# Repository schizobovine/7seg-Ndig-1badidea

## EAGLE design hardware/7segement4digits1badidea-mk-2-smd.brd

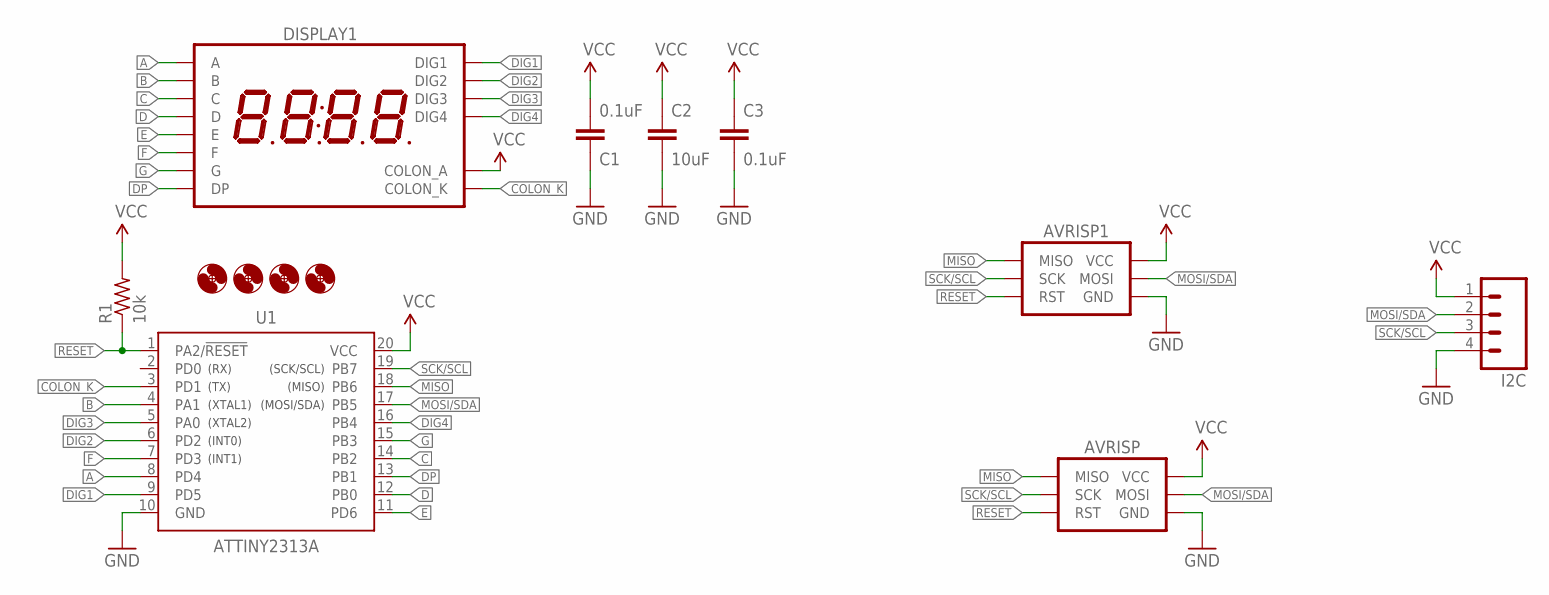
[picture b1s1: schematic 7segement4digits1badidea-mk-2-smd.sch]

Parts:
AVRISP: AVR_SPI_PRG_6PTH; 2X3
AVRISP1: AVR_SPI_PRG_6SMD-RA-FLOPPED-I2C; 1X06-SMD
C1, C3: 0.1uF; C0805
C2: 10uF; C0805
DISPLAY1: 7SED_4DIGIT_14MM14.2MM-CC; 7SEG_4DIG
H1, H2, H3, H4: HOLE#2; HOLE-#2
I2C: M04PTH; 1X04-PTH-VERT
R1: 10k; R0805
U1: ATTINY2313A; SOP20W

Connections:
A: DISPLAY1.P$13 (A), U1.8 (PD4)
B: DISPLAY1.P$9 (B), U1.4 (PA1)
C: DISPLAY1.P$4 (C), U1.14 (PB2)
COLON_K: DISPLAY1.P$7 (COLON_K), U1.3 (PD1)
D: DISPLAY1.P$2 (D), U1.12 (PB0)
DIG1: DISPLAY1.P$14 (DIG1), U1.9 (PD5)
DIG2: DISPLAY1.P$11 (DIG2), U1.6 (PD2)
DIG3: DISPLAY1.P$10 (DIG3), U1.5 (PA0)
DIG4: DISPLAY1.P$6 (DIG4), U1.16 (PB4)
DP: DISPLAY1.P$3 (DP), U1.13 (PB1)
E: DISPLAY1.P$1 (E), U1.11 (PD6)
F: DISPLAY1.P$12 (F), U1.7 (PD3)
G: DISPLAY1.P$5 (G), U1.15 (PB3)
GND: AVRISP.6 (GND), AVRISP1.4 (GND), C1.1, C2.2, C3.2, I2C.4, U1.10 (GND)
MISO: AVRISP.1 (MISO), AVRISP1.5 (MISO), U1.18 (PB6)
MOSI/SDA: AVRISP.4 (MOSI), AVRISP1.3 (MOSI), I2C.2, U1.17 (PB5)
RESET: AVRISP.5 (RST), AVRISP1.6 (RST), R1.1, U1.1 (PA2/!RESET)
SCK/SCL: AVRISP.3 (SCK), AVRISP1.2 (SCK), I2C.3, U1.19 (PB7)
VCC: AVRISP.2 (VCC), AVRISP1.1 (VCC), C1.2, C2.1, C3.1, DISPLAY1.P$8 (COLON_A), I2C.1, R1.2, U1.20 (VCC)

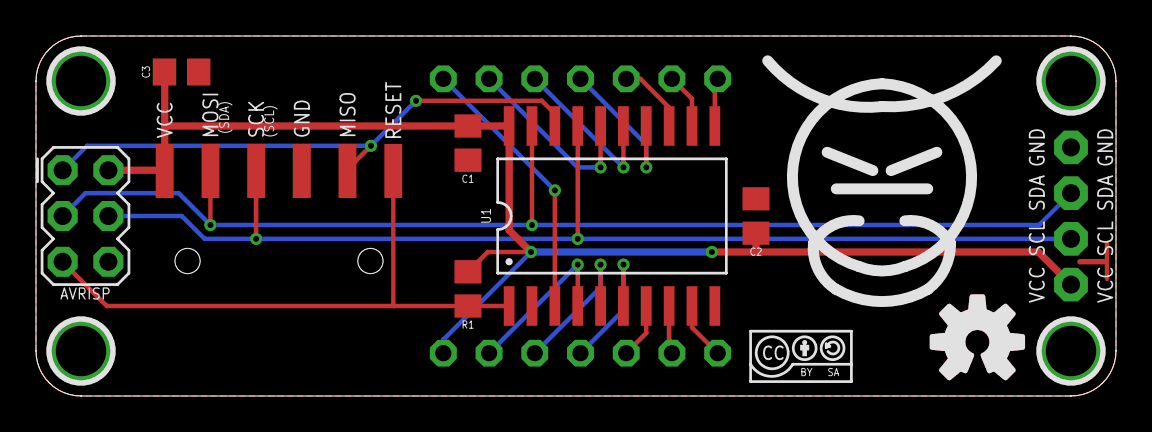
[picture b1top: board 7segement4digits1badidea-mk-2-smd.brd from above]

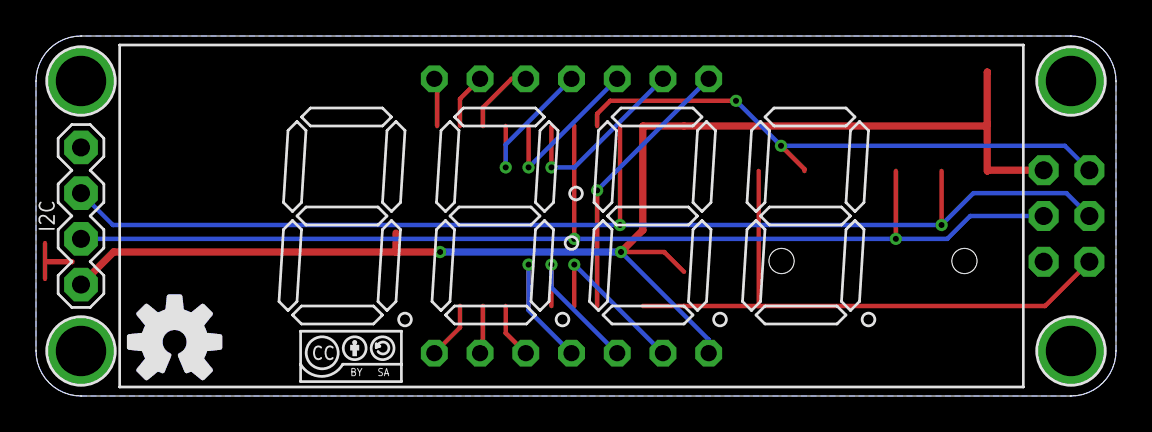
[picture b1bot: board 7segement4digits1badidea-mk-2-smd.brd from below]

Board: 2 copper layers, 60.0 x 20.0 mm, 18 parts (4 on the bottom side), 19 nets.

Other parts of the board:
U$1: COW
U$2, U$5: CC-BY-SA-4.0-NO-URL
U$3, U$4: OSHWLOGO_TOP_0.2_A

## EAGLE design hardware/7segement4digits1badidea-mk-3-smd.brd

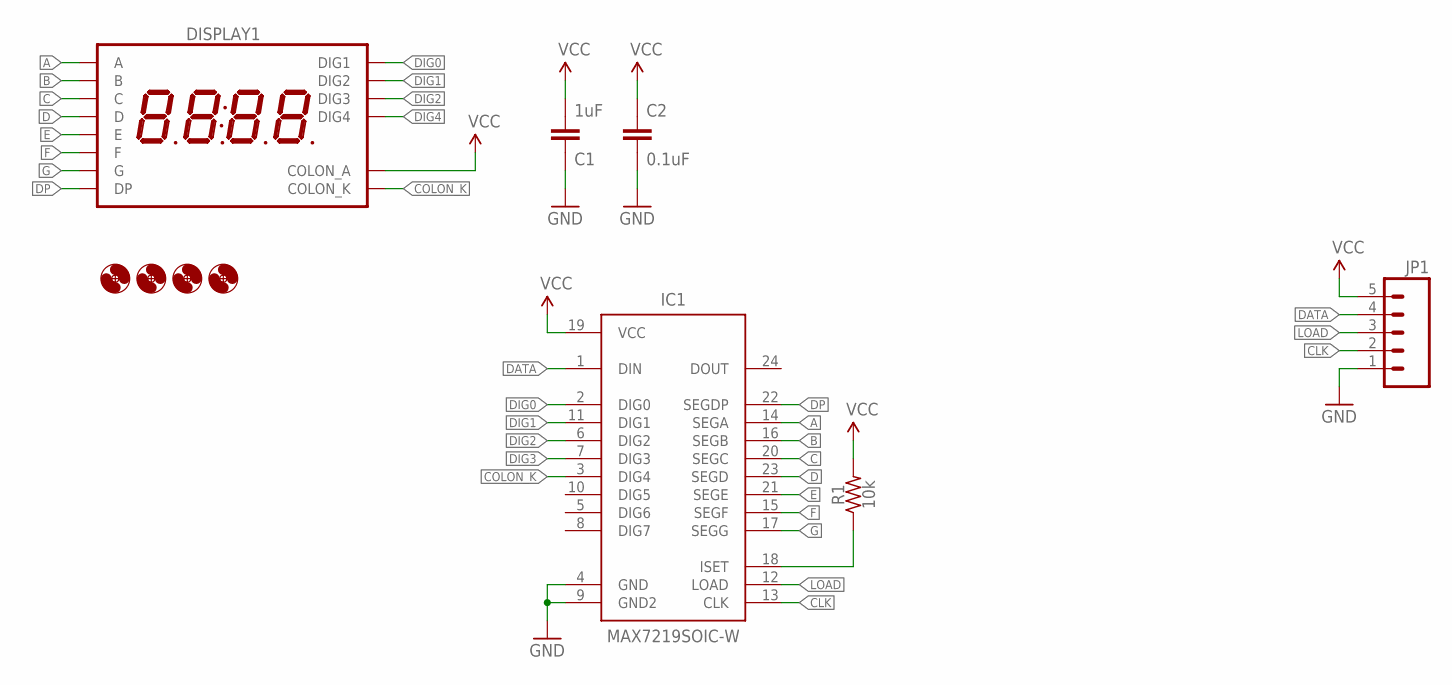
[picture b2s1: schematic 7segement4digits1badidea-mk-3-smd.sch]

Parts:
C1: 1uF; C0805
C2: 0.1uF; C0603
DISPLAY1: 7SEG_4DIGIT_COLONLOLSMDWAT; 7SEG_4DIG_0.56IN_14MM_ADAFRUIT_LOL_SMD_WAT
H1, H2, H3, H4: HOLE#2; HOLE-#2
IC1: MAX7219SOIC-W; SO24W
JP1: M05JST-PH-VERT-PTH; JST-5-PH-VERT-PTH
R1: 10k; R0603

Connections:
A: DISPLAY1.P$13 (A), IC1.14 (SEGA)
B: DISPLAY1.P$9 (B), IC1.16 (SEGB)
C: DISPLAY1.P$4 (C), IC1.20 (SEGC)
CLK: IC1.13 (CLK), JP1.2
COLON_K: DISPLAY1.P$7 (COLON_K), IC1.3 (DIG4)
D: DISPLAY1.P$2 (D), IC1.23 (SEGD)
DATA: IC1.1 (DIN), JP1.4
DIG0: DISPLAY1.P$14 (DIG1), IC1.2 (DIG0)
DIG1: DISPLAY1.P$11 (DIG2), IC1.11 (DIG1)
DIG2: DISPLAY1.P$10 (DIG3), IC1.6 (DIG2)
DIG3: IC1.7 (DIG3)
DIG4: DISPLAY1.P$6 (DIG4)
DP: DISPLAY1.P$3 (DP), IC1.22 (SEGDP)
E: DISPLAY1.P$1 (E), IC1.21 (SEGE)
F: DISPLAY1.P$12 (F), IC1.15 (SEGF)
G: DISPLAY1.P$5 (G), IC1.17 (SEGG)
GND: C1.1, C2.2, IC1.4 (GND), IC1.9 (GND2), JP1.1
LOAD: IC1.12 (LOAD), JP1.3
unnamed: IC1.18 (ISET), R1.1
VCC: C1.2, C2.1, DISPLAY1.P$8 (COLON_A), IC1.19 (VCC), JP1.5, R1.2

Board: 2 copper layers, 14 parts (2 on the bottom side), 18 nets, no tracks yet.

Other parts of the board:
U$1: COW
U$2, U$5: CC-BY-SA-4.0-NO-URL
U$3: OSHWLOGO_TOP_0.2_A

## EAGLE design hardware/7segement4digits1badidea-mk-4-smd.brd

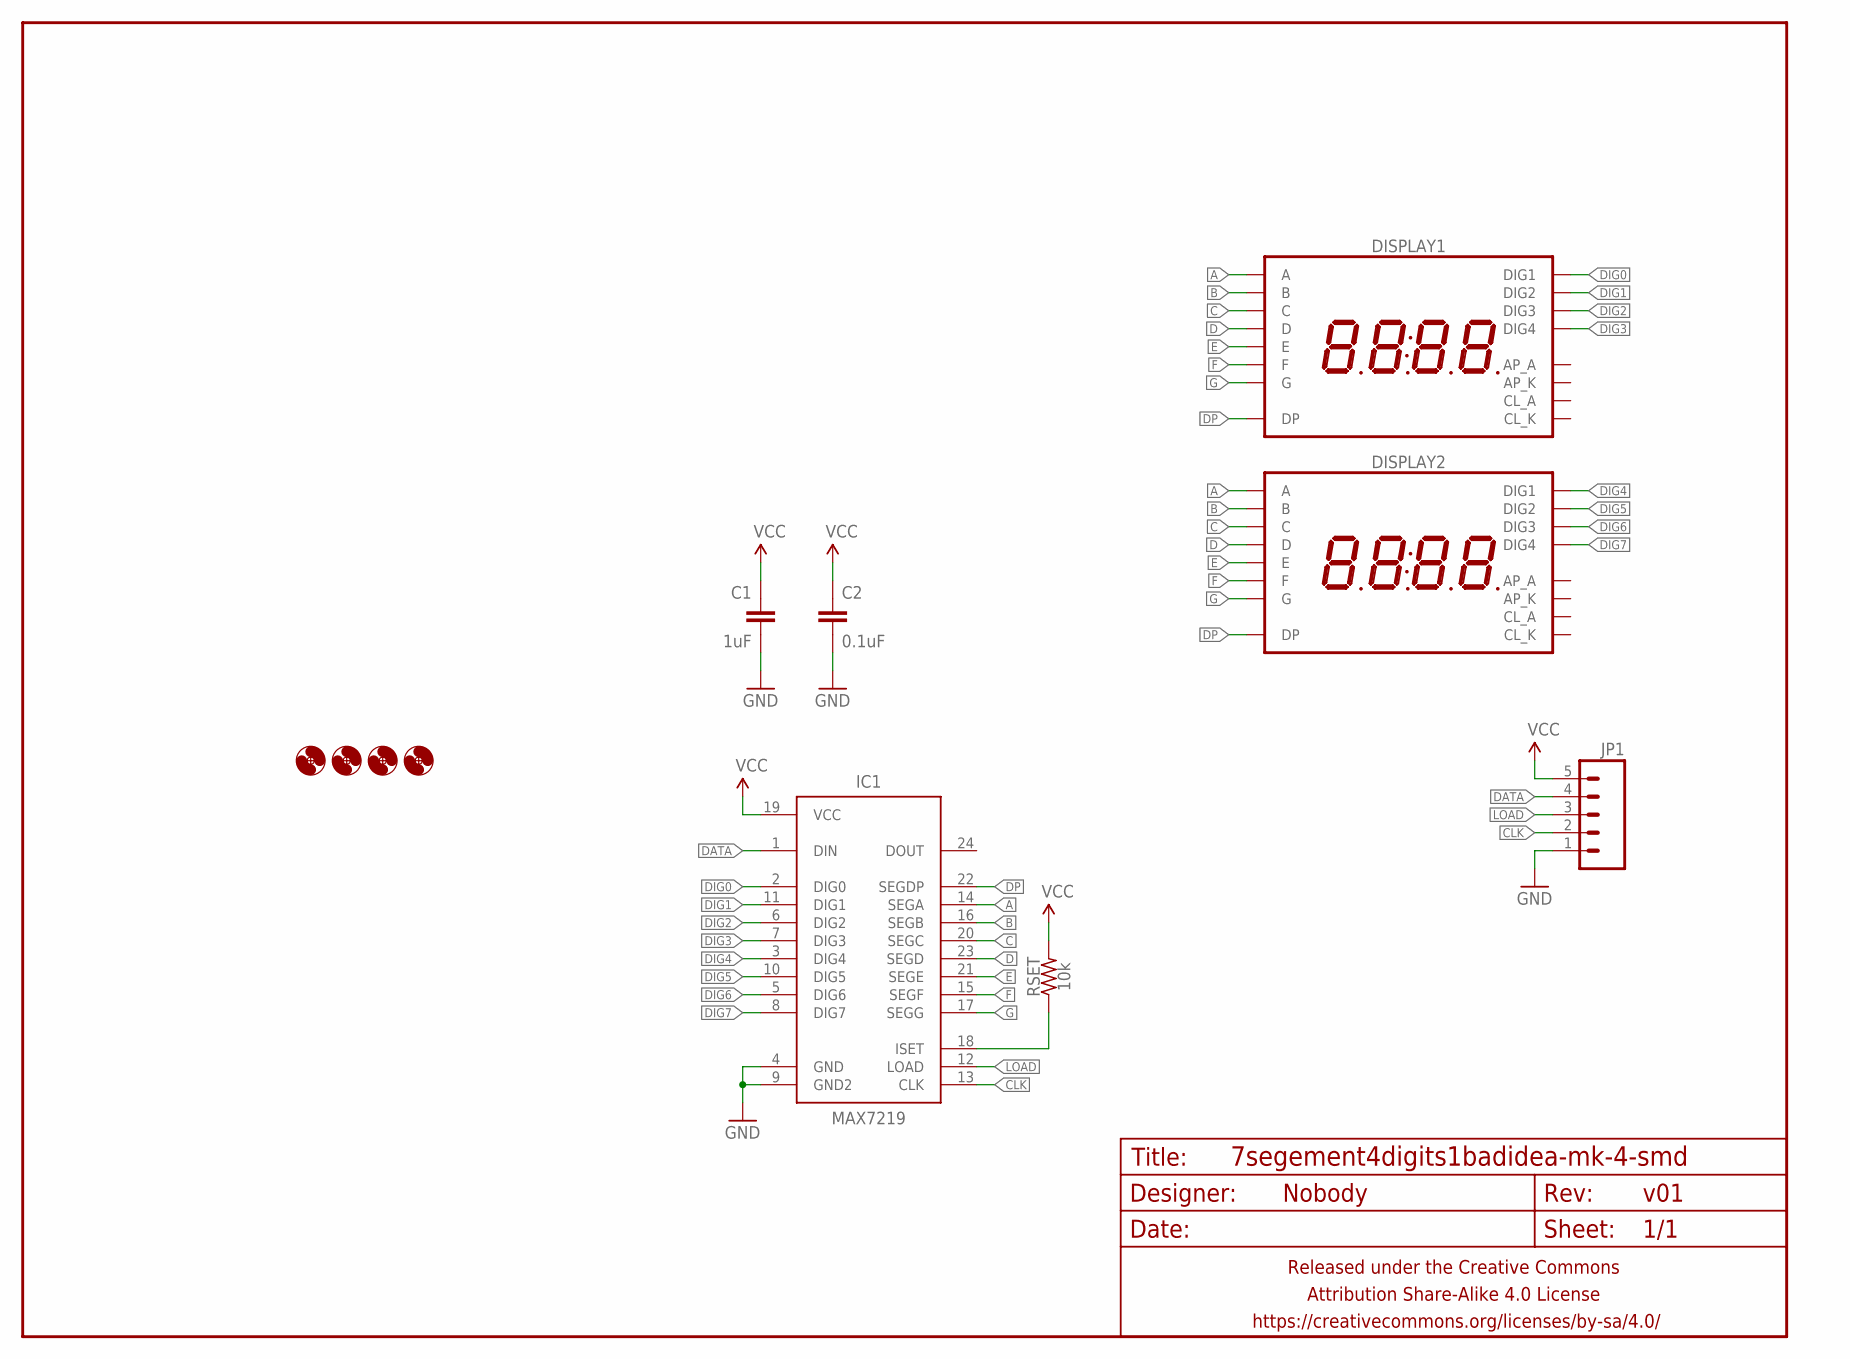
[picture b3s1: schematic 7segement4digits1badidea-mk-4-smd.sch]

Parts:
C1: 1uF; C025-024X044
C2: 0.1uF; C025-024X044
DISPLAY1, DISPLAY2: 7SEG_4DIGIT_COLON_APOS; 7SEG_4DIG_10MM
FRAME1: FRAME-LETTERNO_PACKAGE; DUMMY
H1, H2, H3, H4: HOLE#2; HOLE-#2
IC1: MAX7219; SO24W
JP1: M05PTH; 1X05
RSET: 10k; RESISTOR-AXIAL-PTH-6.35MM

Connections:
A: DISPLAY1.14 (A), DISPLAY2.14 (A), IC1.14 (SEGA)
B: DISPLAY1.16 (B), DISPLAY2.16 (B), IC1.16 (SEGB)
C: DISPLAY1.13 (C), DISPLAY2.13 (C), IC1.20 (SEGC)
CLK: IC1.13 (CLK), JP1.2
D: DISPLAY1.3 (D), DISPLAY2.3 (D), IC1.23 (SEGD)
DATA: IC1.1 (DIN), JP1.4
DIG0: DISPLAY1.1 (DIG1), IC1.2 (DIG0)
DIG1: DISPLAY1.2 (DIG2), IC1.11 (DIG1)
DIG2: DISPLAY1.6 (DIG3), IC1.6 (DIG2)
DIG3: DISPLAY1.8 (DIG4), IC1.7 (DIG3)
DIG4: DISPLAY2.1 (DIG1), IC1.3 (DIG4)
DIG5: DISPLAY2.2 (DIG2), IC1.10 (DIG5)
DIG6: DISPLAY2.6 (DIG3), IC1.5 (DIG6)
DIG7: DISPLAY2.8 (DIG4), IC1.8 (DIG7)
DP: DISPLAY1.7 (DP), DISPLAY2.7 (DP), IC1.22 (SEGDP)
E: DISPLAY1.5 (E), DISPLAY2.5 (E), IC1.21 (SEGE)
F: DISPLAY1.11 (F), DISPLAY2.11 (F), IC1.15 (SEGF)
G: DISPLAY1.15 (G), DISPLAY2.15 (G), IC1.17 (SEGG)
GND: C1.2, C2.2, IC1.4 (GND), IC1.9 (GND2), JP1.1
LOAD: IC1.12 (LOAD), JP1.3
unnamed: IC1.18 (ISET), RSET.P$1 (1)
VCC: C1.1, C2.1, IC1.19 (VCC), JP1.5, RSET.P$2 (2)

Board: 2 copper layers, 12 parts (2 on the bottom side), 22 nets, no tracks yet.

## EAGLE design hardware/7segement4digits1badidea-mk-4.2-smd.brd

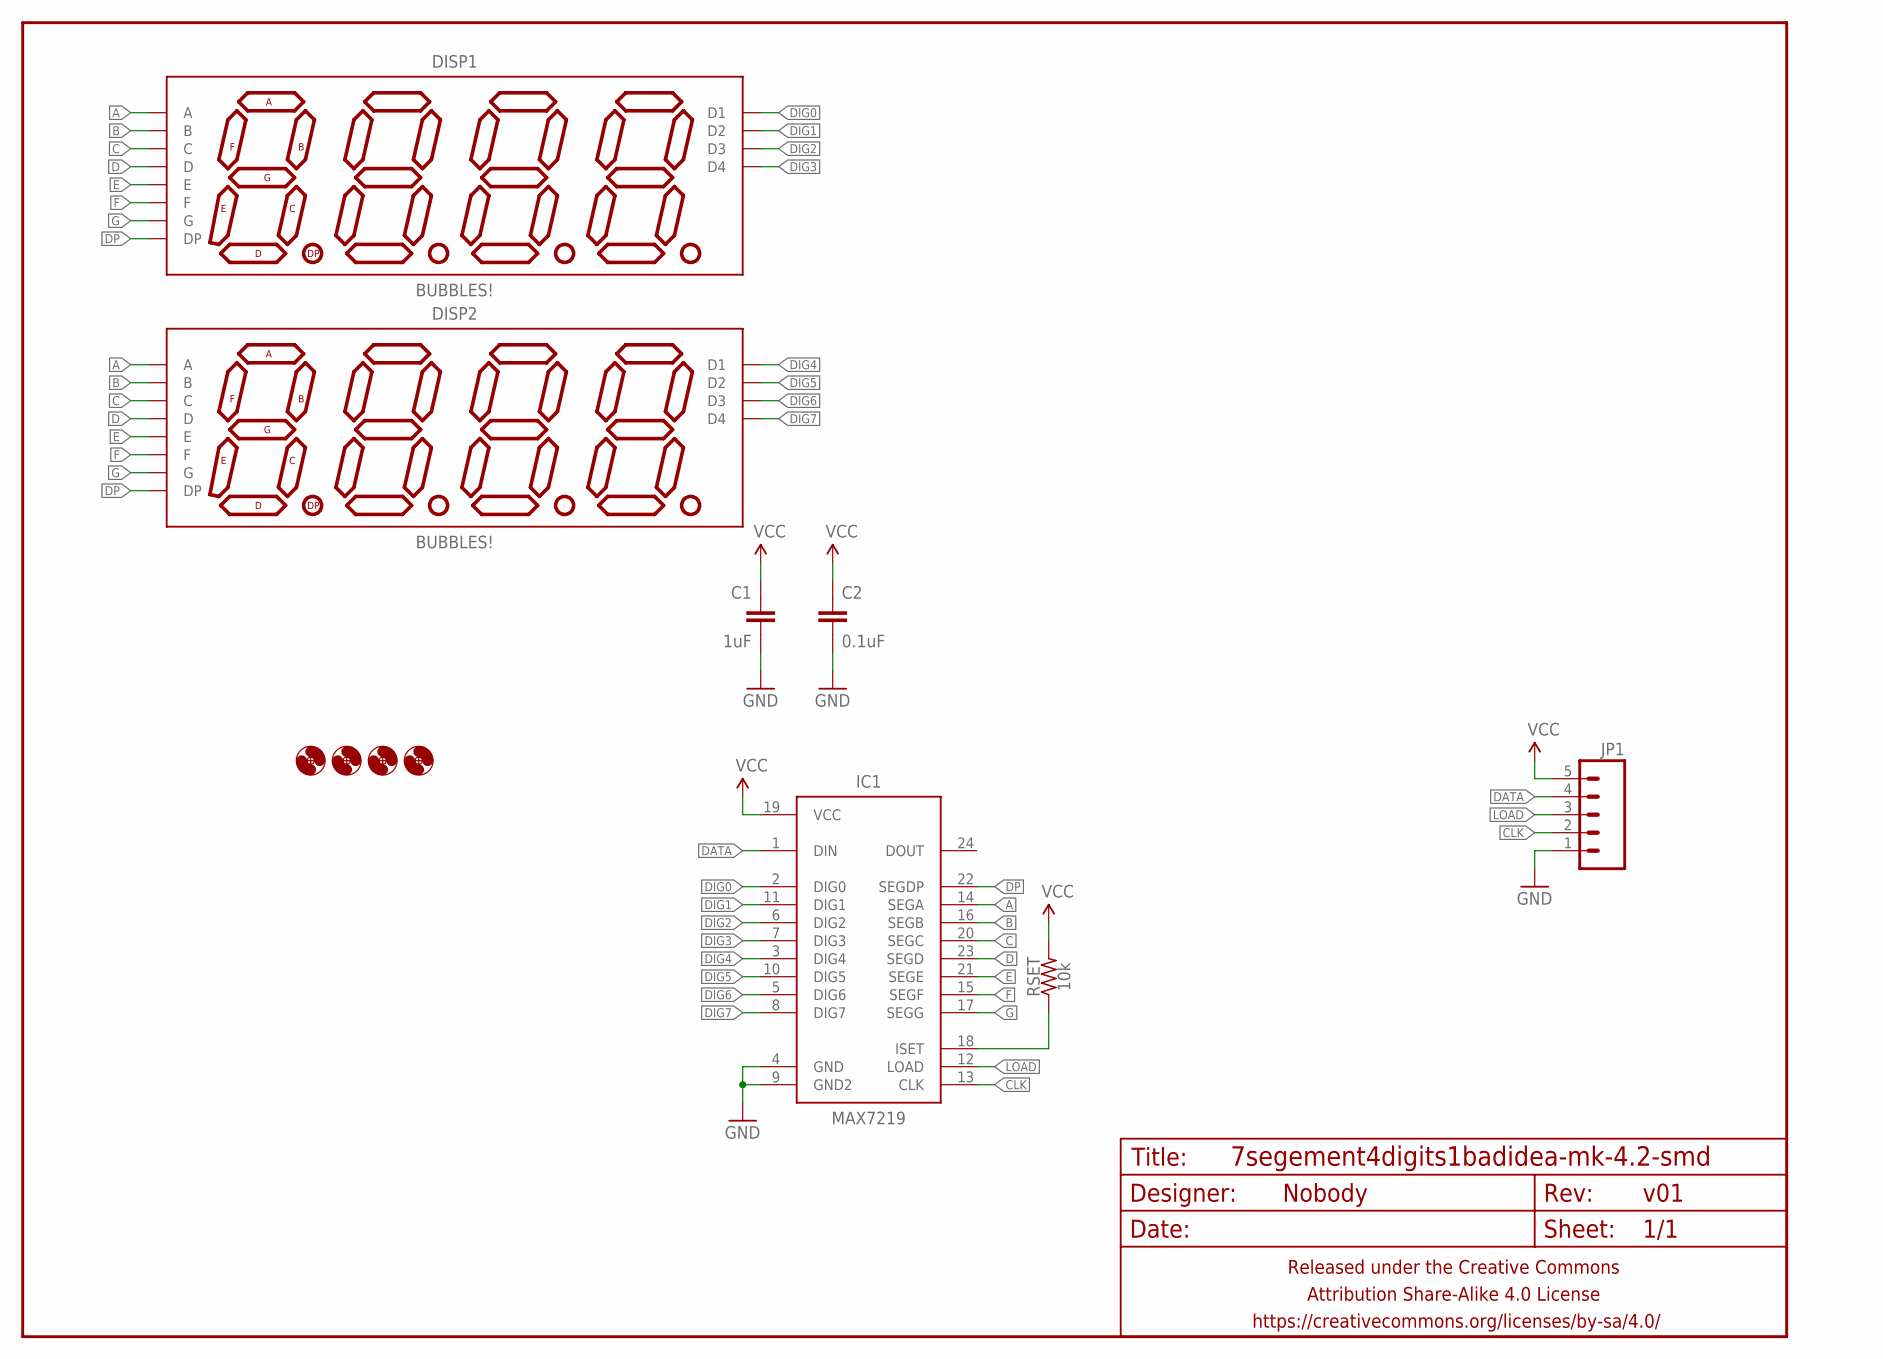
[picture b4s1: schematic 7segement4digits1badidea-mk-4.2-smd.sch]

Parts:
C1: 1uF; C025-024X044
C2: 0.1uF; C025-024X044
DISP1, DISP2: BUBBLES!; DIL12
FRAME1: FRAME-LETTERNO_PACKAGE; DUMMY
H1, H2, H3, H4: HOLE#2; HOLE-#2
IC1: MAX7219; SO24W
JP1: M05PTH; 1X05
RSET: 10k; RESISTOR-AXIAL-PTH-6.35MM

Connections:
A: DISP1.12 (A), DISP2.12 (A), IC1.14 (SEGA)
B: DISP1.11 (B), DISP2.11 (B), IC1.16 (SEGB)
C: DISP1.3 (C), DISP2.3 (C), IC1.20 (SEGC)
CLK: IC1.13 (CLK), JP1.2
D: DISP1.8 (D), DISP2.8 (D), IC1.23 (SEGD)
DATA: IC1.1 (DIN), JP1.4
DIG0: DISP1.1 (D1), IC1.2 (DIG0)
DIG1: DISP1.10 (D2), IC1.11 (DIG1)
DIG2: DISP1.4 (D3), IC1.6 (DIG2)
DIG3: DISP1.6 (D4), IC1.7 (DIG3)
DIG4: DISP2.1 (D1), IC1.3 (DIG4)
DIG5: DISP2.10 (D2), IC1.10 (DIG5)
DIG6: DISP2.4 (D3), IC1.5 (DIG6)
DIG7: DISP2.6 (D4), IC1.8 (DIG7)
DP: DISP1.5 (DP), DISP2.5 (DP), IC1.22 (SEGDP)
E: DISP1.2 (E), DISP2.2 (E), IC1.21 (SEGE)
F: DISP1.9 (F), DISP2.9 (F), IC1.15 (SEGF)
G: DISP1.7 (G), DISP2.7 (G), IC1.17 (SEGG)
GND: C1.2, C2.2, IC1.4 (GND), IC1.9 (GND2), JP1.1
LOAD: IC1.12 (LOAD), JP1.3
unnamed: IC1.18 (ISET), RSET.P$1 (1)
VCC: C1.1, C2.1, IC1.19 (VCC), JP1.5, RSET.P$2 (2)

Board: 2 copper layers, 12 parts (0 on the bottom side), 22 nets, no tracks yet.

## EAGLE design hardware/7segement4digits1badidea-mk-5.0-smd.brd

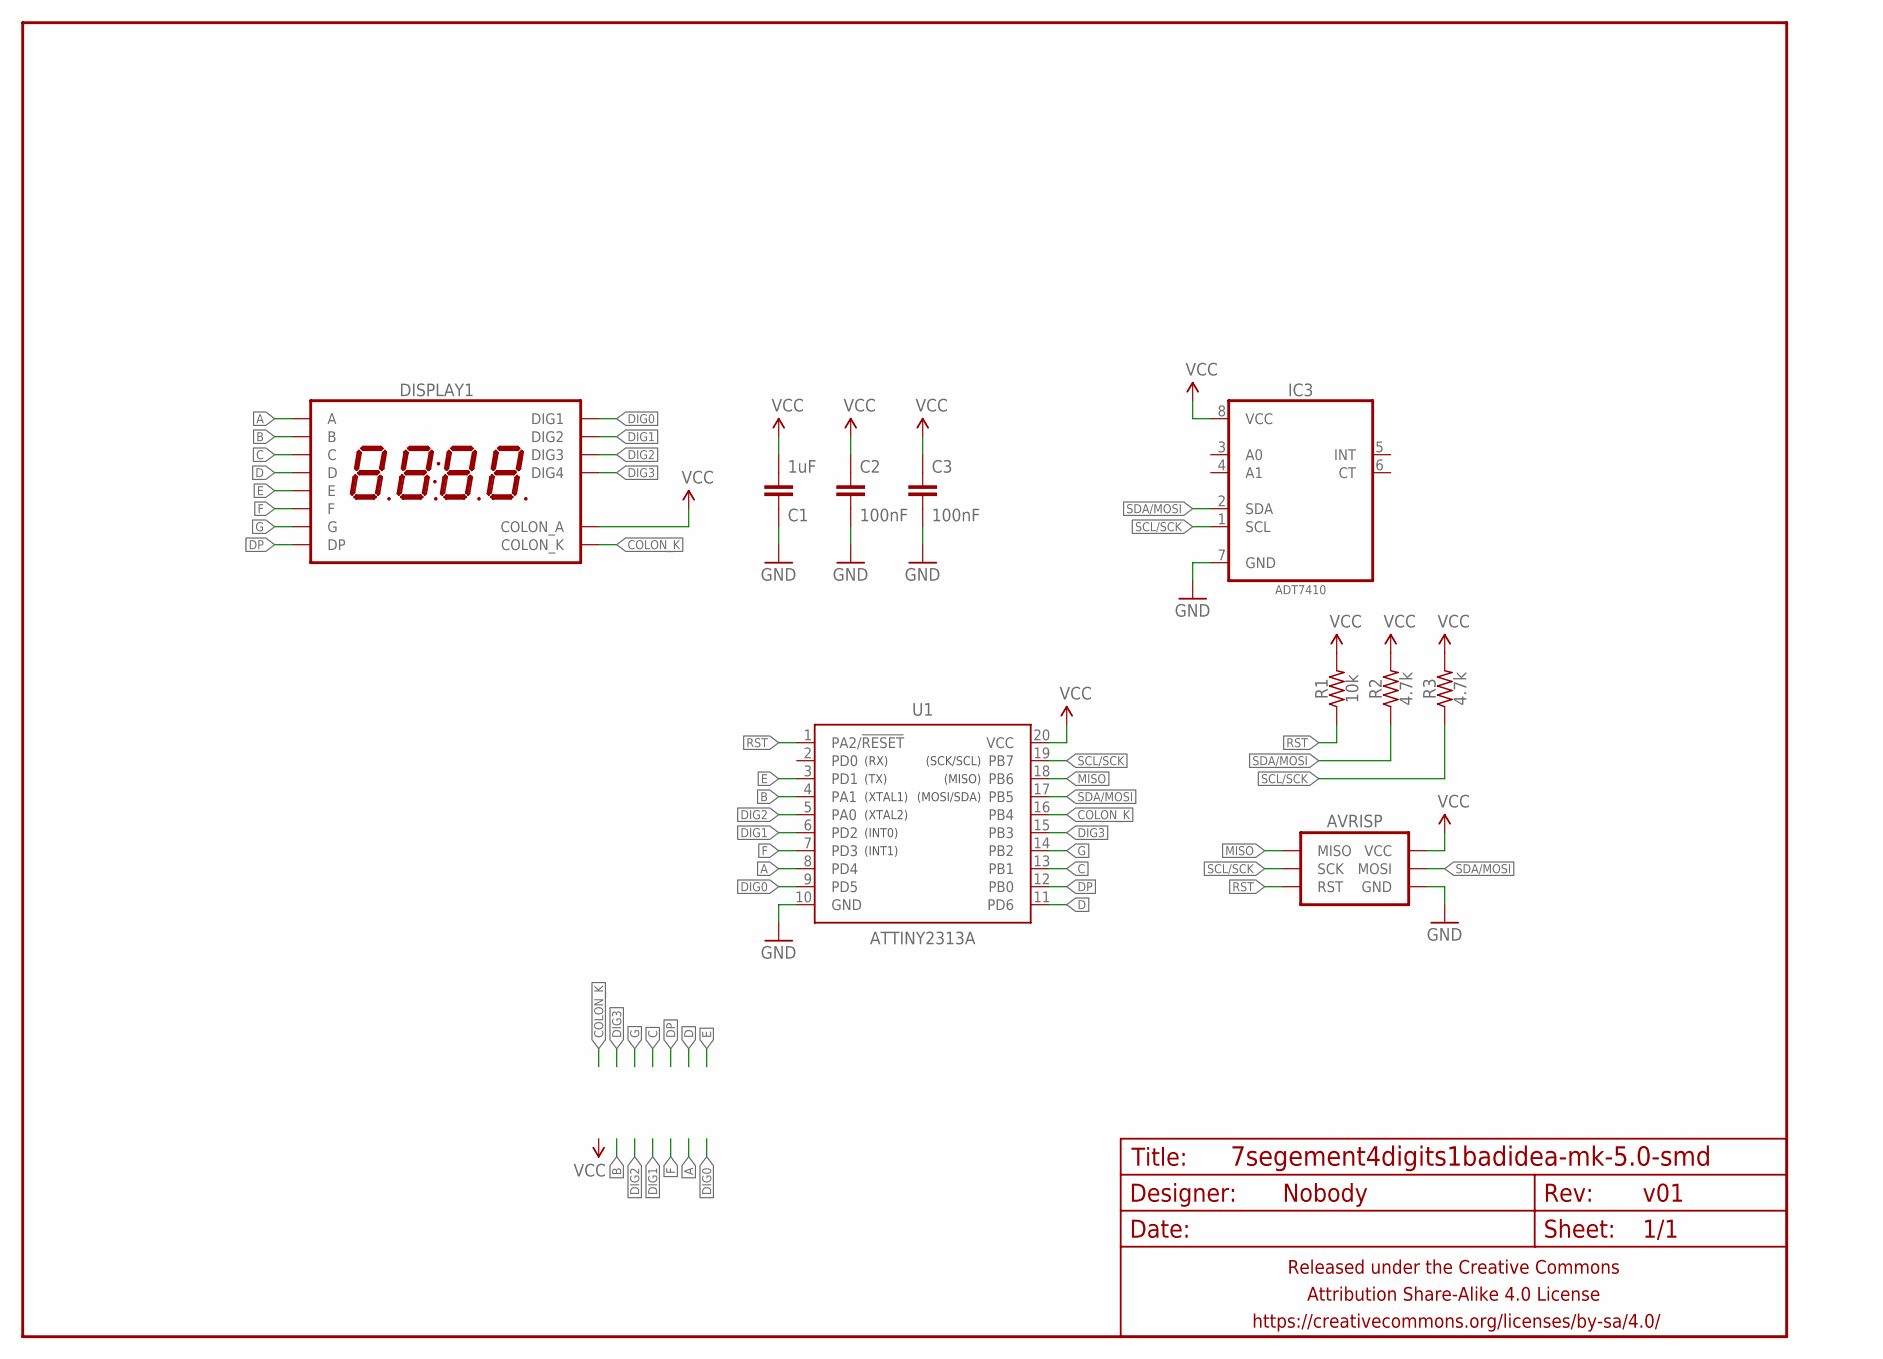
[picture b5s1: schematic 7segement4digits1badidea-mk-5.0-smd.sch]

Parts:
AVRISP: AVR_SPI_PRG_6AVR-JST-PTH-RA-I2C; AVR-JST-6-PTH-RA-I2C
C1: 1uF; C0805
C2, C3: 100nF; C0805
DISPLAY1: 7SEG_4DIGIT_COLONADAFRUIT_0.56IN; 7SEG_4DIG
FRAME1: FRAME-LETTERNO_PACKAGE; DUMMY
IC3: ADT7410; SOIC127P600X175-8N
R1: 10k; R0805
R2, R3: 4.7k; R0805
U1: ATTINY2313A; SOIC20W-SLIM

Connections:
A: DISPLAY1.P$13 (A), U1.8 (PD4)
B: DISPLAY1.P$9 (B), U1.4 (PA1)
C: DISPLAY1.P$4 (C), U1.13 (PB1)
COLON_K: DISPLAY1.P$7 (COLON_K), U1.16 (PB4)
D: DISPLAY1.P$2 (D), U1.11 (PD6)
DIG0: DISPLAY1.P$14 (DIG1), U1.9 (PD5)
DIG1: DISPLAY1.P$11 (DIG2), U1.6 (PD2)
DIG2: DISPLAY1.P$10 (DIG3), U1.5 (PA0)
DIG3: DISPLAY1.P$6 (DIG4), U1.15 (PB3)
DP: DISPLAY1.P$3 (DP), U1.12 (PB0)
E: DISPLAY1.P$1 (E), U1.3 (PD1)
F: DISPLAY1.P$12 (F), U1.7 (PD3)
G: DISPLAY1.P$5 (G), U1.14 (PB2)
GND: AVRISP.GND, C1.1, C2.2, C3.2, IC3.7 (GND), U1.10 (GND)
MISO: AVRISP.MISO, U1.18 (PB6)
RST: AVRISP.RESET (RST), R1.1, U1.1 (PA2/!RESET)
SCL/SCK: AVRISP.SCK, IC3.1 (SCL), R3.1, U1.19 (PB7)
SDA/MOSI: AVRISP.MOSI/SDA (MOSI), IC3.2 (SDA), R2.1, U1.17 (PB5)
VCC: AVRISP.VCC, C1.2, C2.1, C3.1, DISPLAY1.P$8 (COLON_A), IC3.8 (VCC), R1.2, R2.2, R3.2, U1.20 (VCC)

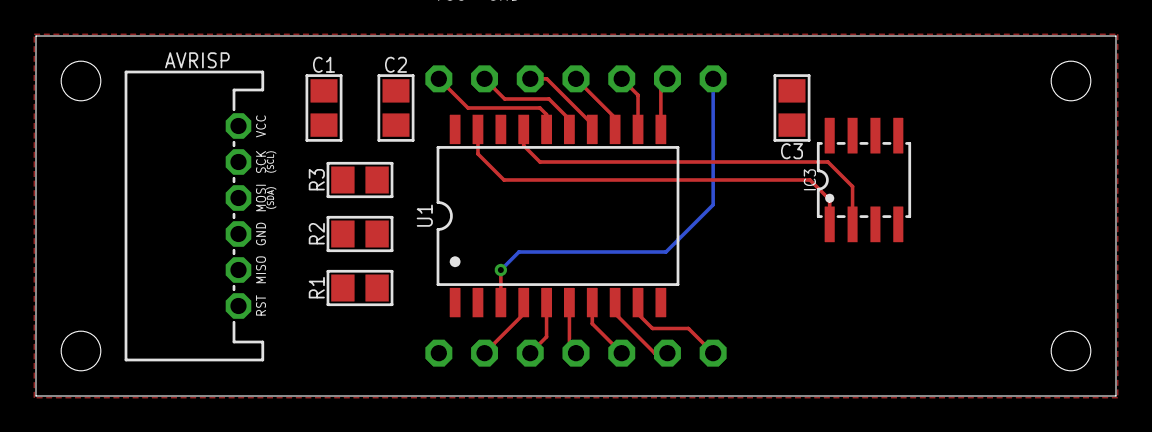
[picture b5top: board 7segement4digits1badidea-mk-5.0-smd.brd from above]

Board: 2 copper layers, 60.0 x 20.0 mm, 11 parts (1 on the bottom side), 19 nets.

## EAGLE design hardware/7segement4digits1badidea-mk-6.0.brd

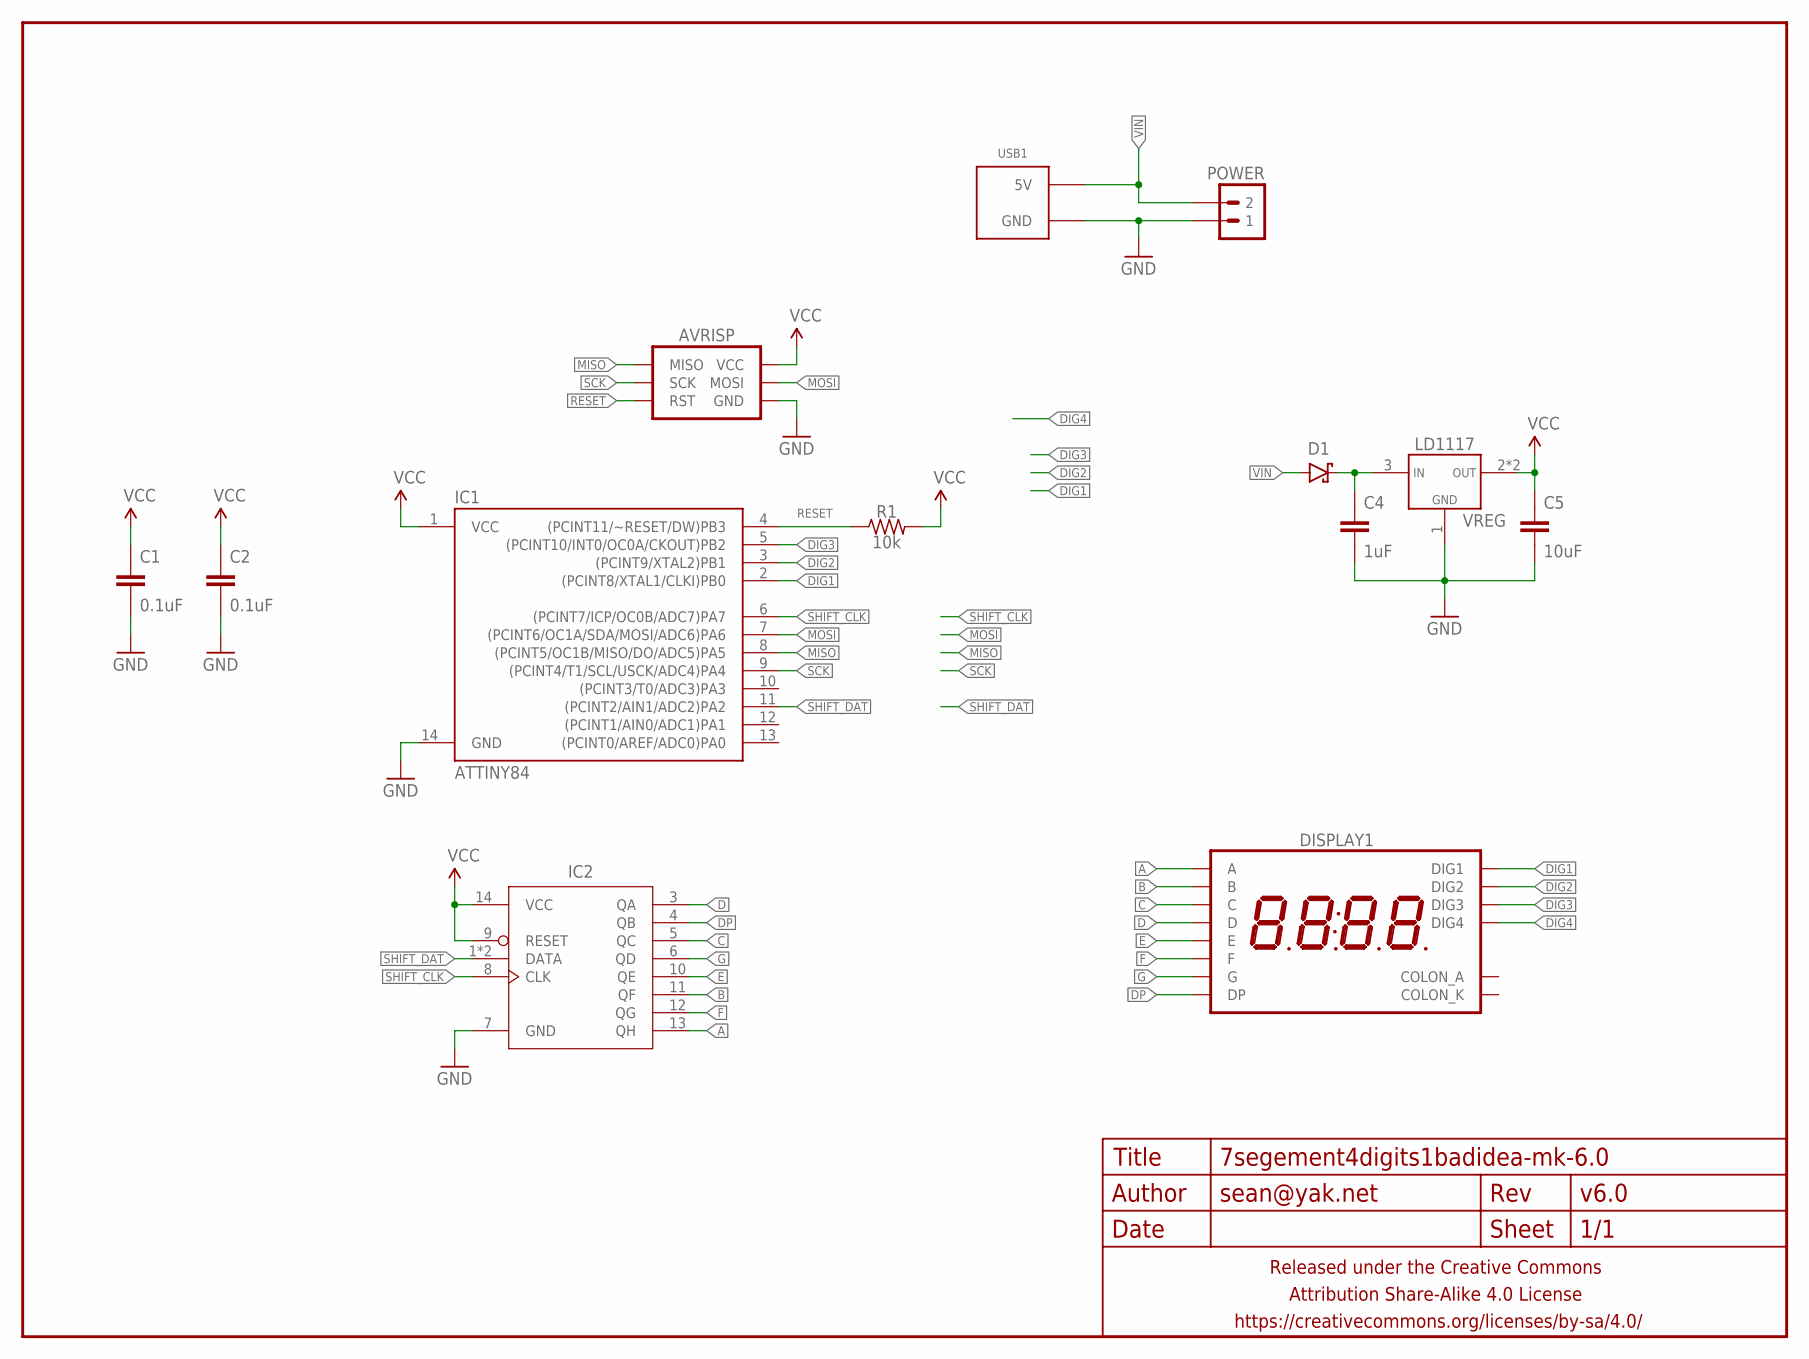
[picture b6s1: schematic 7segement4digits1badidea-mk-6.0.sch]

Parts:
AVRISP: AVR_SPI_PRG_6TESTPOINTS; 2X3_TEST_POINTS
C1, C2: 0.1uF; C0603
C4: 1uF; C0805
C5: 10uF; C0805
D1: DIODE-SCHOTTKYSOD123; SOD123-SCHOTTKY
DISPLAY1: 7SEG_4DIGIT_COLON14.2MM-CC; 7SEG_4DIG_0.56IN_14MM_ADAFRUIT
FRAME1: FRAME-LETTERNO_PACKAGE; DUMMY
IC1: ATTINY84; SO14
IC2: 74HC164; SO14
POWER: M02PTH-CENTERED-R+; 1X02-CENTER-R+
R1: 10k; R0603
USB1: USB_AB_PWRONLY; FCI-10103594-USB-MICRO-B-PWRONLY
VREG: LD1117; SOT223

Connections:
A: IC2.13 (QH)
B: IC2.11 (QF)
C: IC2.5 (QC)
D: IC2.3 (QA)
DIG1: IC1.2 ((PCINT8/XTAL1/CLKI)PB0)
DIG2: IC1.3 ((PCINT9/XTAL2)PB1)
DIG3: IC1.5 ((PCINT10/INT0/OC0A/CKOUT)PB2)
DIG4: DISPLAY1.P$6 (DIG4)
DP: IC2.4 (QB)
E: IC2.10 (QE)
F: IC2.12 (QG)
G: IC2.6 (QD)
GND: AVRISP.6 (GND), C1.2, C2.2, C4.2, C5.2, IC1.14 (GND), IC2.7 (GND), POWER.1, USB1.5 (GND), USB1.SHIELD@1 (GND), USB1.SHIELD@2 (GND), USB1.SHIELD@3 (GND), USB1.SHIELD@4 (GND), VREG.1 (GND)
MISO: AVRISP.1 (MISO), IC1.8 ((PCINT5/OC1B/MISO/DO/ADC5)PA5)
MOSI: AVRISP.4 (MOSI), IC1.7 ((PCINT6/OC1A/SDA/MOSI/ADC6)PA6)
unnamed: C4.1, D1.C, VREG.3 (VIN)
RESET: AVRISP.5 (RST), IC1.4 ((PCINT11/~RESET/DW)PB3), R1.1
SCK: AVRISP.3 (SCK), IC1.9 ((PCINT4/T1/SCL/USCK/ADC4)PA4)
SHIFT_CLK: IC1.6 ((PCINT7/ICP/OC0B/ADC7)PA7), IC2.8 (CLK)
SHIFT_DAT: IC1.11 ((PCINT2/AIN1/ADC2)PA2), IC2.1 (DATA), IC2.2 (DATA)
VCC: AVRISP.2 (VCC), C1.1, C2.1, C5.1, IC1.1 (VCC), IC2.9 (RESET), IC2.14 (VCC), R1.2, VREG.2 (VOUT), VREG.4 (VOUT)
VIN: D1.A, POWER.2, USB1.1 (5V)

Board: 2 copper layers, 14 parts (2 on the bottom side), 10 nets, no tracks yet.

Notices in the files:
parts and their libraries:
A_butts: Released under the Creative Commons Attribution Share-Alike 4.0 License
A_butts: https://creativecommons.org/licenses/by-sa/4.0
A_butts: Released under the Creative Commons
